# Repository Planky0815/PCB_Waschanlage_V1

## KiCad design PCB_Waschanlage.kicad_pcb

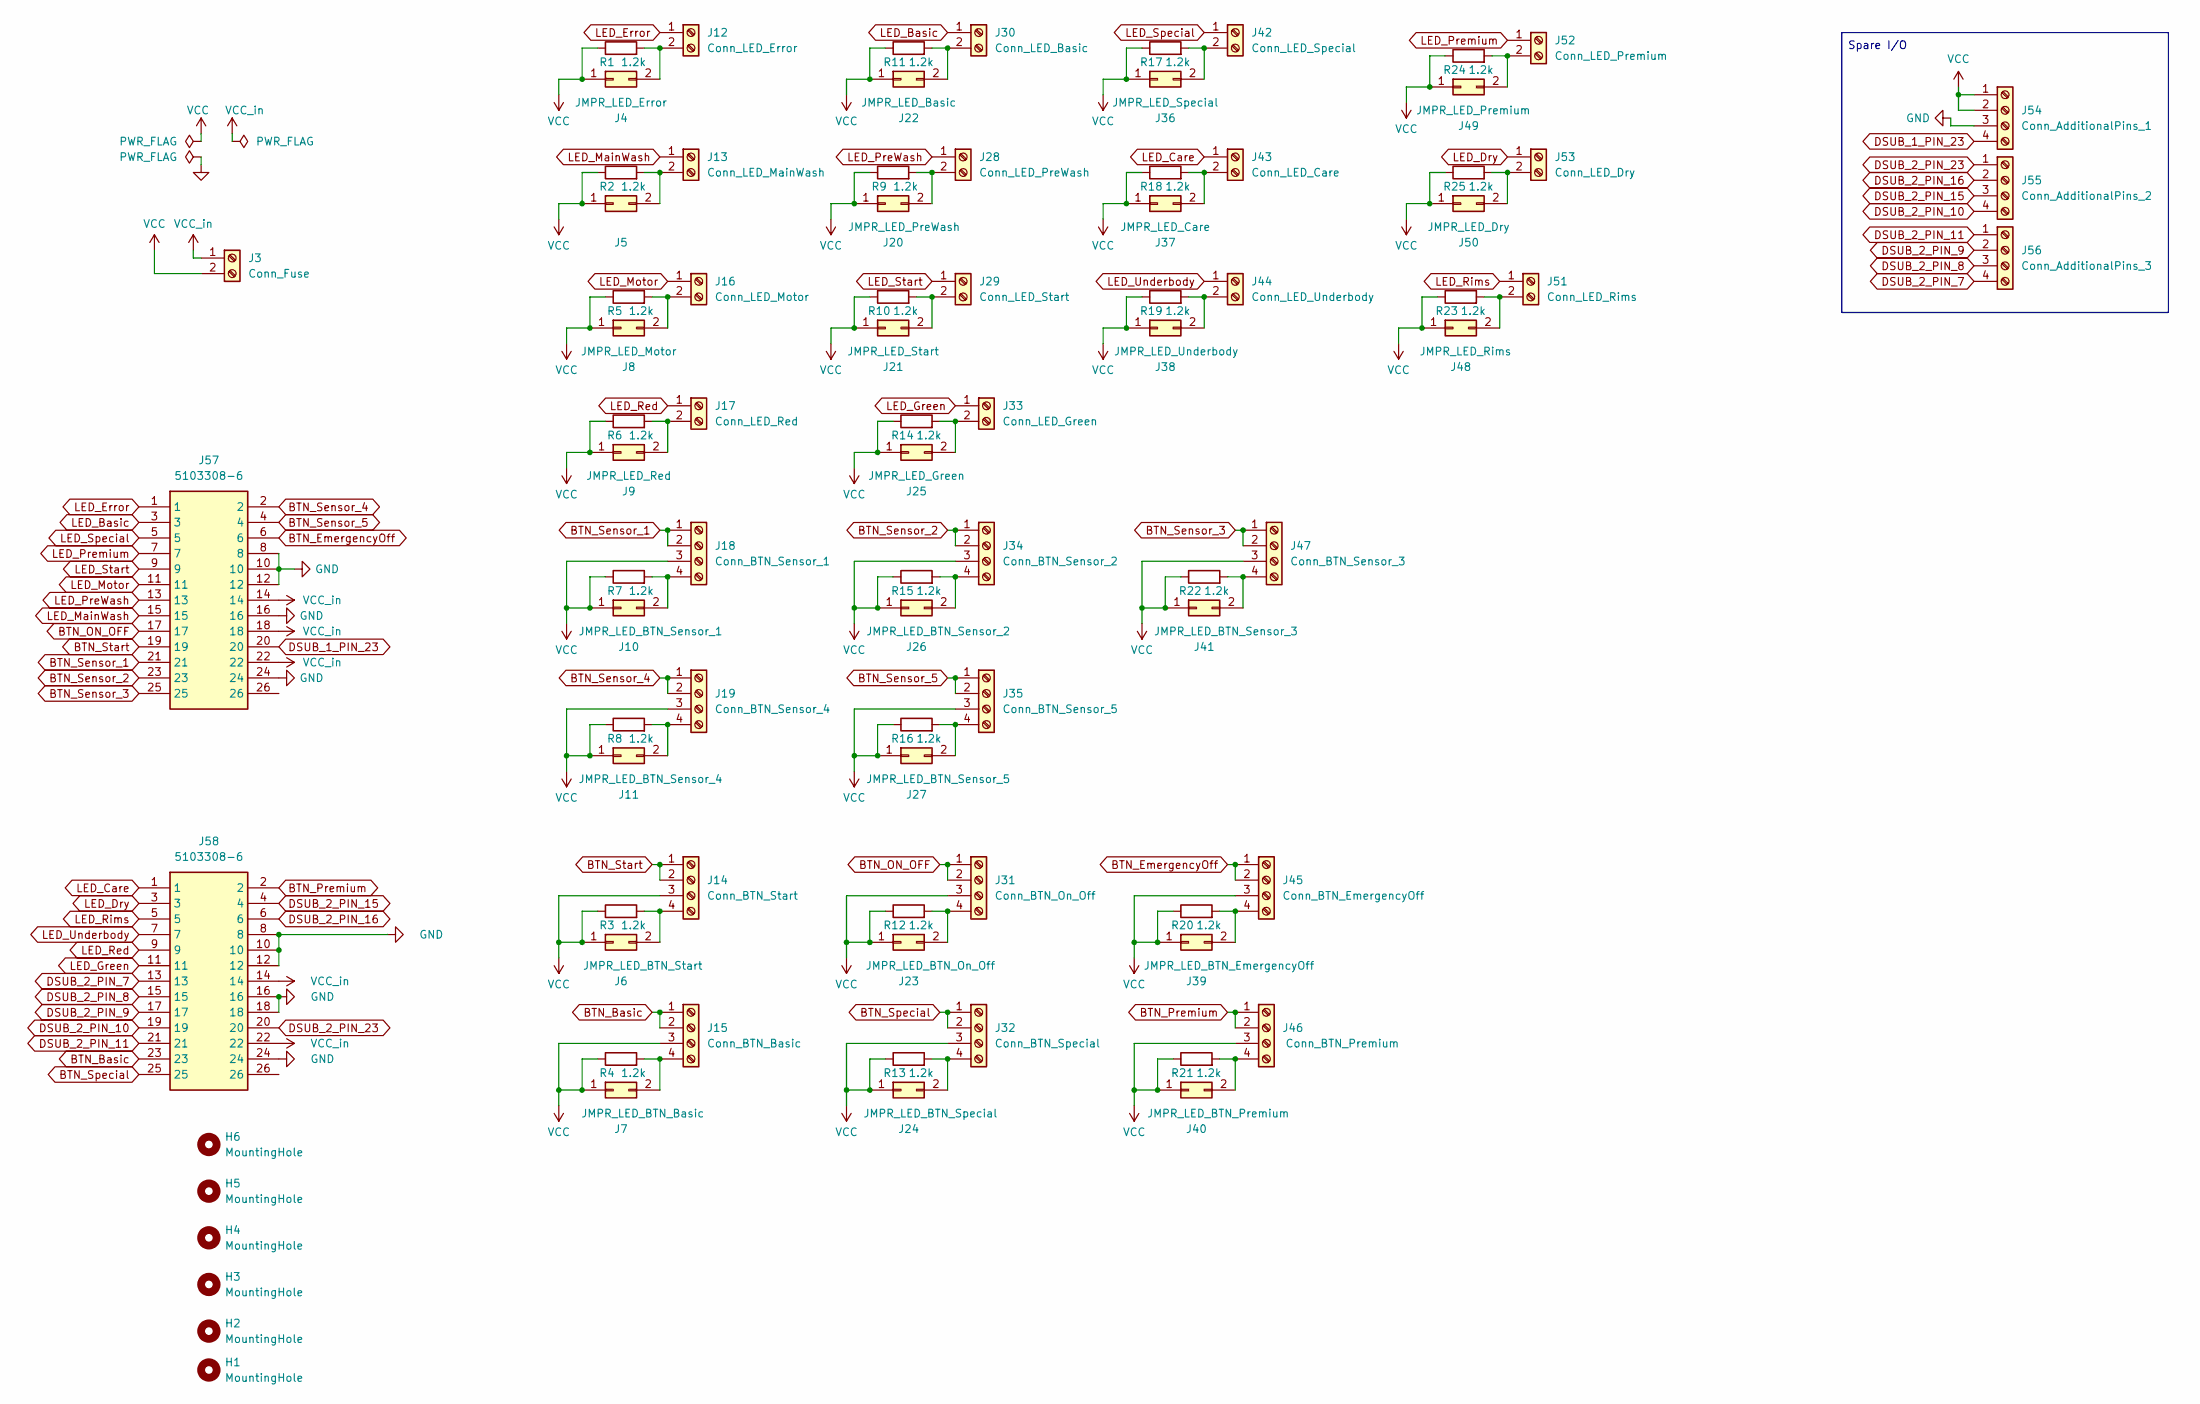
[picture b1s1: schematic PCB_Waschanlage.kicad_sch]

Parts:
H1, H2, H3, H4, H5, H6: MountingHole; MountingHole_4.3mm_M4
J3: Conn_Fuse; CUI_TBL002A-350-02GY-2GY
J4: JMPR_LED_Error; PinHeader_1x02_P2.54mm_Vertical
J5: JMPR_LED_MainWash; PinHeader_1x02_P2.54mm_Vertical
J6: JMPR_LED_BTN_Start; PinHeader_1x02_P2.54mm_Vertical
J7: JMPR_LED_BTN_Basic; PinHeader_1x02_P2.54mm_Vertical
J8: JMPR_LED_Motor; PinHeader_1x02_P2.54mm_Vertical
J9: JMPR_LED_Red; PinHeader_1x02_P2.54mm_Vertical
J10: JMPR_LED_BTN_Sensor_1; PinHeader_1x02_P2.54mm_Vertical
J11: JMPR_LED_BTN_Sensor_4; PinHeader_1x02_P2.54mm_Vertical
J12: Conn_LED_Error; CUI_TBL002A-350-02GY-2GY
J13: Conn_LED_MainWash; CUI_TBL002A-350-02GY-2GY
J14: Conn_BTN_Start; CUI_TBL002A-350-04GY-2GY
J15: Conn_BTN_Basic; CUI_TBL002A-350-04GY-2GY
J16: Conn_LED_Motor; CUI_TBL002A-350-02GY-2GY
J17: Conn_LED_Red; CUI_TBL002A-350-02GY-2GY
J18: Conn_BTN_Sensor_1; CUI_TBL002A-350-04GY-2GY
J19: Conn_BTN_Sensor_4; CUI_TBL002A-350-04GY-2GY
J20: JMPR_LED_PreWash; PinHeader_1x02_P2.54mm_Vertical
J21: JMPR_LED_Start; PinHeader_1x02_P2.54mm_Vertical
J22: JMPR_LED_Basic; PinHeader_1x02_P2.54mm_Vertical
J23: JMPR_LED_BTN_On_Off; PinHeader_1x02_P2.54mm_Vertical
J24: JMPR_LED_BTN_Special; PinHeader_1x02_P2.54mm_Vertical
J25: JMPR_LED_Green; PinHeader_1x02_P2.54mm_Vertical
J26: JMPR_LED_BTN_Sensor_2; PinHeader_1x02_P2.54mm_Vertical
J27: JMPR_LED_BTN_Sensor_5; PinHeader_1x02_P2.54mm_Vertical
J28: Conn_LED_PreWash; CUI_TBL002A-350-02GY-2GY
J29: Conn_LED_Start; CUI_TBL002A-350-02GY-2GY
J30: Conn_LED_Basic; CUI_TBL002A-350-02GY-2GY
J31: Conn_BTN_On_Off; CUI_TBL002A-350-04GY-2GY
J32: Conn_BTN_Special; CUI_TBL002A-350-04GY-2GY
J33: Conn_LED_Green; CUI_TBL002A-350-02GY-2GY
J34: Conn_BTN_Sensor_2; CUI_TBL002A-350-04GY-2GY
J35: Conn_BTN_Sensor_5; CUI_TBL002A-350-04GY-2GY
J36: JMPR_LED_Special; PinHeader_1x02_P2.54mm_Vertical
J37: JMPR_LED_Care; PinHeader_1x02_P2.54mm_Vertical
J38: JMPR_LED_Underbody; PinHeader_1x02_P2.54mm_Vertical
J39: JMPR_LED_BTN_EmergencyOff; PinHeader_1x02_P2.54mm_Vertical
J40: JMPR_LED_BTN_Premium; PinHeader_1x02_P2.54mm_Vertical
J41: JMPR_LED_BTN_Sensor_3; PinHeader_1x02_P2.54mm_Vertical
J42: Conn_LED_Special; CUI_TBL002A-350-02GY-2GY
J43: Conn_LED_Care; CUI_TBL002A-350-02GY-2GY
J44: Conn_LED_Underbody; CUI_TBL002A-350-02GY-2GY
J45: Conn_BTN_EmergencyOff; CUI_TBL002A-350-04GY-2GY
J46: Conn_BTN_Premium; CUI_TBL002A-350-04GY-2GY
J47: Conn_BTN_Sensor_3; CUI_TBL002A-350-04GY-2GY
J48: JMPR_LED_Rims; PinHeader_1x02_P2.54mm_Vertical
J49: JMPR_LED_Premium; PinHeader_1x02_P2.54mm_Vertical
J50: JMPR_LED_Dry; PinHeader_1x02_P2.54mm_Vertical
J51: Conn_LED_Rims; CUI_TBL002A-350-02GY-2GY
J52: Conn_LED_Premium; CUI_TBL002A-350-02GY-2GY
J53: Conn_LED_Dry; CUI_TBL002A-350-02GY-2GY
J54: Conn_AdditionalPins_1; CUI_TBL002A-350-04GY-2GY
J55: Conn_AdditionalPins_2; CUI_TBL002A-350-04GY-2GY
J56: Conn_AdditionalPins_3; CUI_TBL002A-350-04GY-2GY
J57, J58: 5103308-6; SHDR26W66P254_2X13_4051X914X986P; Manufacturer_Part_Number 5103308-6; Mouser Part Number 571-5103308-6
R1, R2, R3, R4, R5, R6, R7, R8, R9, R10, R11, R12, R13, R14, R15, R16, R17, R18, R19, R20, R21, R22, R23, R24, R25: 1.2k; R_Axial_DIN0204_L3.6mm_D1.6mm_P7.62mm_Horizontal

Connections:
BTN_Basic: J15.1, J15.2, J58.23
BTN_EmergencyOff: J45.1, J45.2, J57.6
BTN_ON_OFF: J31.1, J31.2, J57.17
BTN_Premium: J46.1, J46.2, J58.2
BTN_Sensor_1: J18.1, J18.2, J57.21
BTN_Sensor_2: J34.1, J34.2, J57.23
BTN_Sensor_3: J47.1, J47.2, J57.25
BTN_Sensor_4: J19.1, J19.2, J57.2
BTN_Sensor_5: J35.1, J35.2, J57.4
BTN_Special: J32.1, J32.2, J58.25
BTN_Start: J14.1, J14.2, J57.19
DSUB_1_PIN_23: J54.4, J57.20
DSUB_2_PIN_7: J56.4, J58.13
DSUB_2_PIN_8: J56.3, J58.15
DSUB_2_PIN_9: J56.2, J58.17
DSUB_2_PIN_10: J55.4, J58.19
DSUB_2_PIN_11: J56.1, J58.21
DSUB_2_PIN_15: J55.3, J58.4
DSUB_2_PIN_16: J55.2, J58.6
DSUB_2_PIN_23: J55.1, J58.20
GND: J54.3, J57.8, J57.10, J57.12, J57.16, J57.24, J58.8, J58.10, J58.12, J58.16, J58.18, J58.24
LED_Basic: J30.1, J57.3
LED_Care: J43.1, J58.1
LED_Dry: J53.1, J58.3
LED_Error: J12.1, J57.1
LED_Green: J33.1, J58.11
LED_MainWash: J13.1, J57.15
LED_Motor: J16.1, J57.11
LED_PreWash: J28.1, J57.13
LED_Premium: J52.1, J57.7
LED_Red: J17.1, J58.9
LED_Rims: J51.1, J58.5
LED_Special: J42.1, J57.5
LED_Start: J29.1, J57.9
LED_Underbody: J44.1, J58.7
unnamed: J10.2, J18.4, R7.2
unnamed: J11.2, J19.4, R8.2
unnamed: J4.2, J12.2, R1.2
unnamed: J5.2, J13.2, R2.2
unnamed: J6.2, J14.4, R3.2
unnamed: J7.2, J15.4, R4.2
unnamed: J8.2, J16.2, R5.2
unnamed: J9.2, J17.2, R6.2
unnamed: J20.2, J28.2, R9.2
unnamed: J21.2, J29.2, R10.2
unnamed: J22.2, J30.2, R11.2
unnamed: J23.2, J31.4, R12.2
unnamed: J24.2, J32.4, R13.2
unnamed: J25.2, J33.2, R14.2
unnamed: J26.2, J34.4, R15.2
unnamed: J27.2, J35.4, R16.2
unnamed: J36.2, J42.2, R17.2
unnamed: J37.2, J43.2, R18.2
unnamed: J38.2, J44.2, R19.2
unnamed: J39.2, J45.4, R20.2
unnamed: J40.2, J46.4, R21.2
unnamed: J41.2, J47.4, R22.2
unnamed: J48.2, J51.2, R23.2
unnamed: J49.2, J52.2, R24.2
unnamed: J50.2, J53.2, R25.2
VCC: J3.2, J4.1, J5.1, J6.1, J7.1, J8.1, J9.1, J10.1, J11.1, J14.3, J15.3, J18.3, J19.3, J20.1, J21.1, J22.1, J23.1, J24.1, J25.1, J26.1, J27.1, J31.3, J32.3, J34.3, J35.3, J36.1, J37.1, J38.1, J39.1, J40.1, J41.1, J45.3, J46.3, J47.3, J48.1, J49.1, J50.1, J54.1, J54.2, R1.1, R2.1, R3.1, R4.1, R5.1, R6.1, R7.1, R8.1, R9.1, R10.1, R11.1, R12.1, R13.1, R14.1, R15.1, R16.1, R17.1, R18.1, R19.1, R20.1, R21.1, R22.1, R23.1, R24.1, R25.1
VCC_in: J3.1, J57.14, J57.18, J57.22, J58.14, J58.22

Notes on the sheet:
Spare I/O

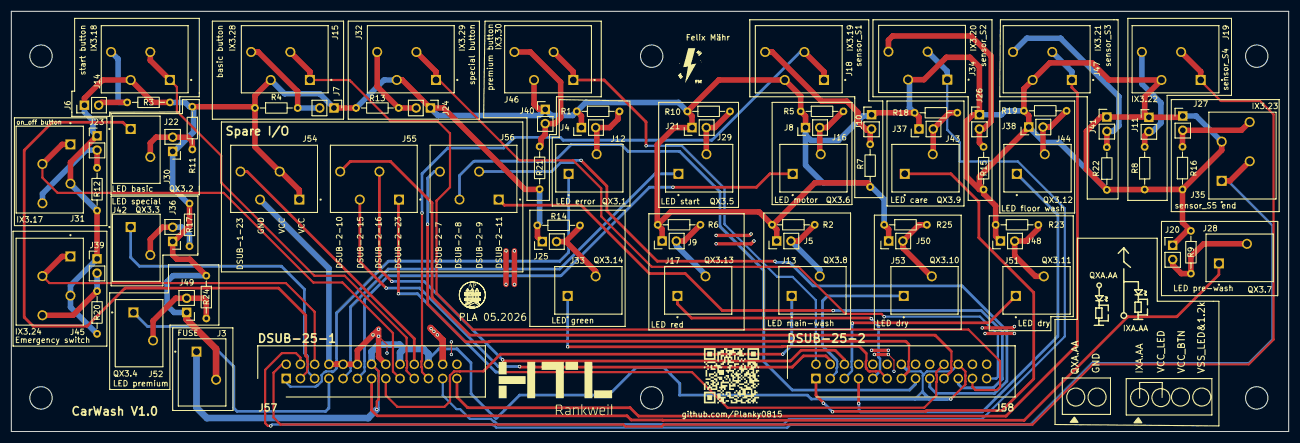
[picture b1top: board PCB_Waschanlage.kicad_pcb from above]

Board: 2 copper layers, 228.0 x 75.0 mm, 87 parts (0 on the bottom side), 62 nets.

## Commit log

2026-04-29 initial gitignor commit
2026-04-29 added info files
2026-05-20 Changed Connectors and Rerouting
2026-05-20 Added new connectors on the PCB
2026-05-24 Routing fimished
2026-05-24 Silkscreen added
2026-05-24 added text ToDos
2026-05-24 Design finished. open: only review
2026-05-27 Added Datasheet, Created BOM, Included Links to Connectors
2026-05-27 Checked Dimensions, Added Link to Connectors, Added Datasheet
2026-05-27 updated BOM, added Datasheet
2026-05-27 Created Gerber Files
2026-05-28 Bug fixes
2026-05-29 all done
2026-05-29 production file generated
